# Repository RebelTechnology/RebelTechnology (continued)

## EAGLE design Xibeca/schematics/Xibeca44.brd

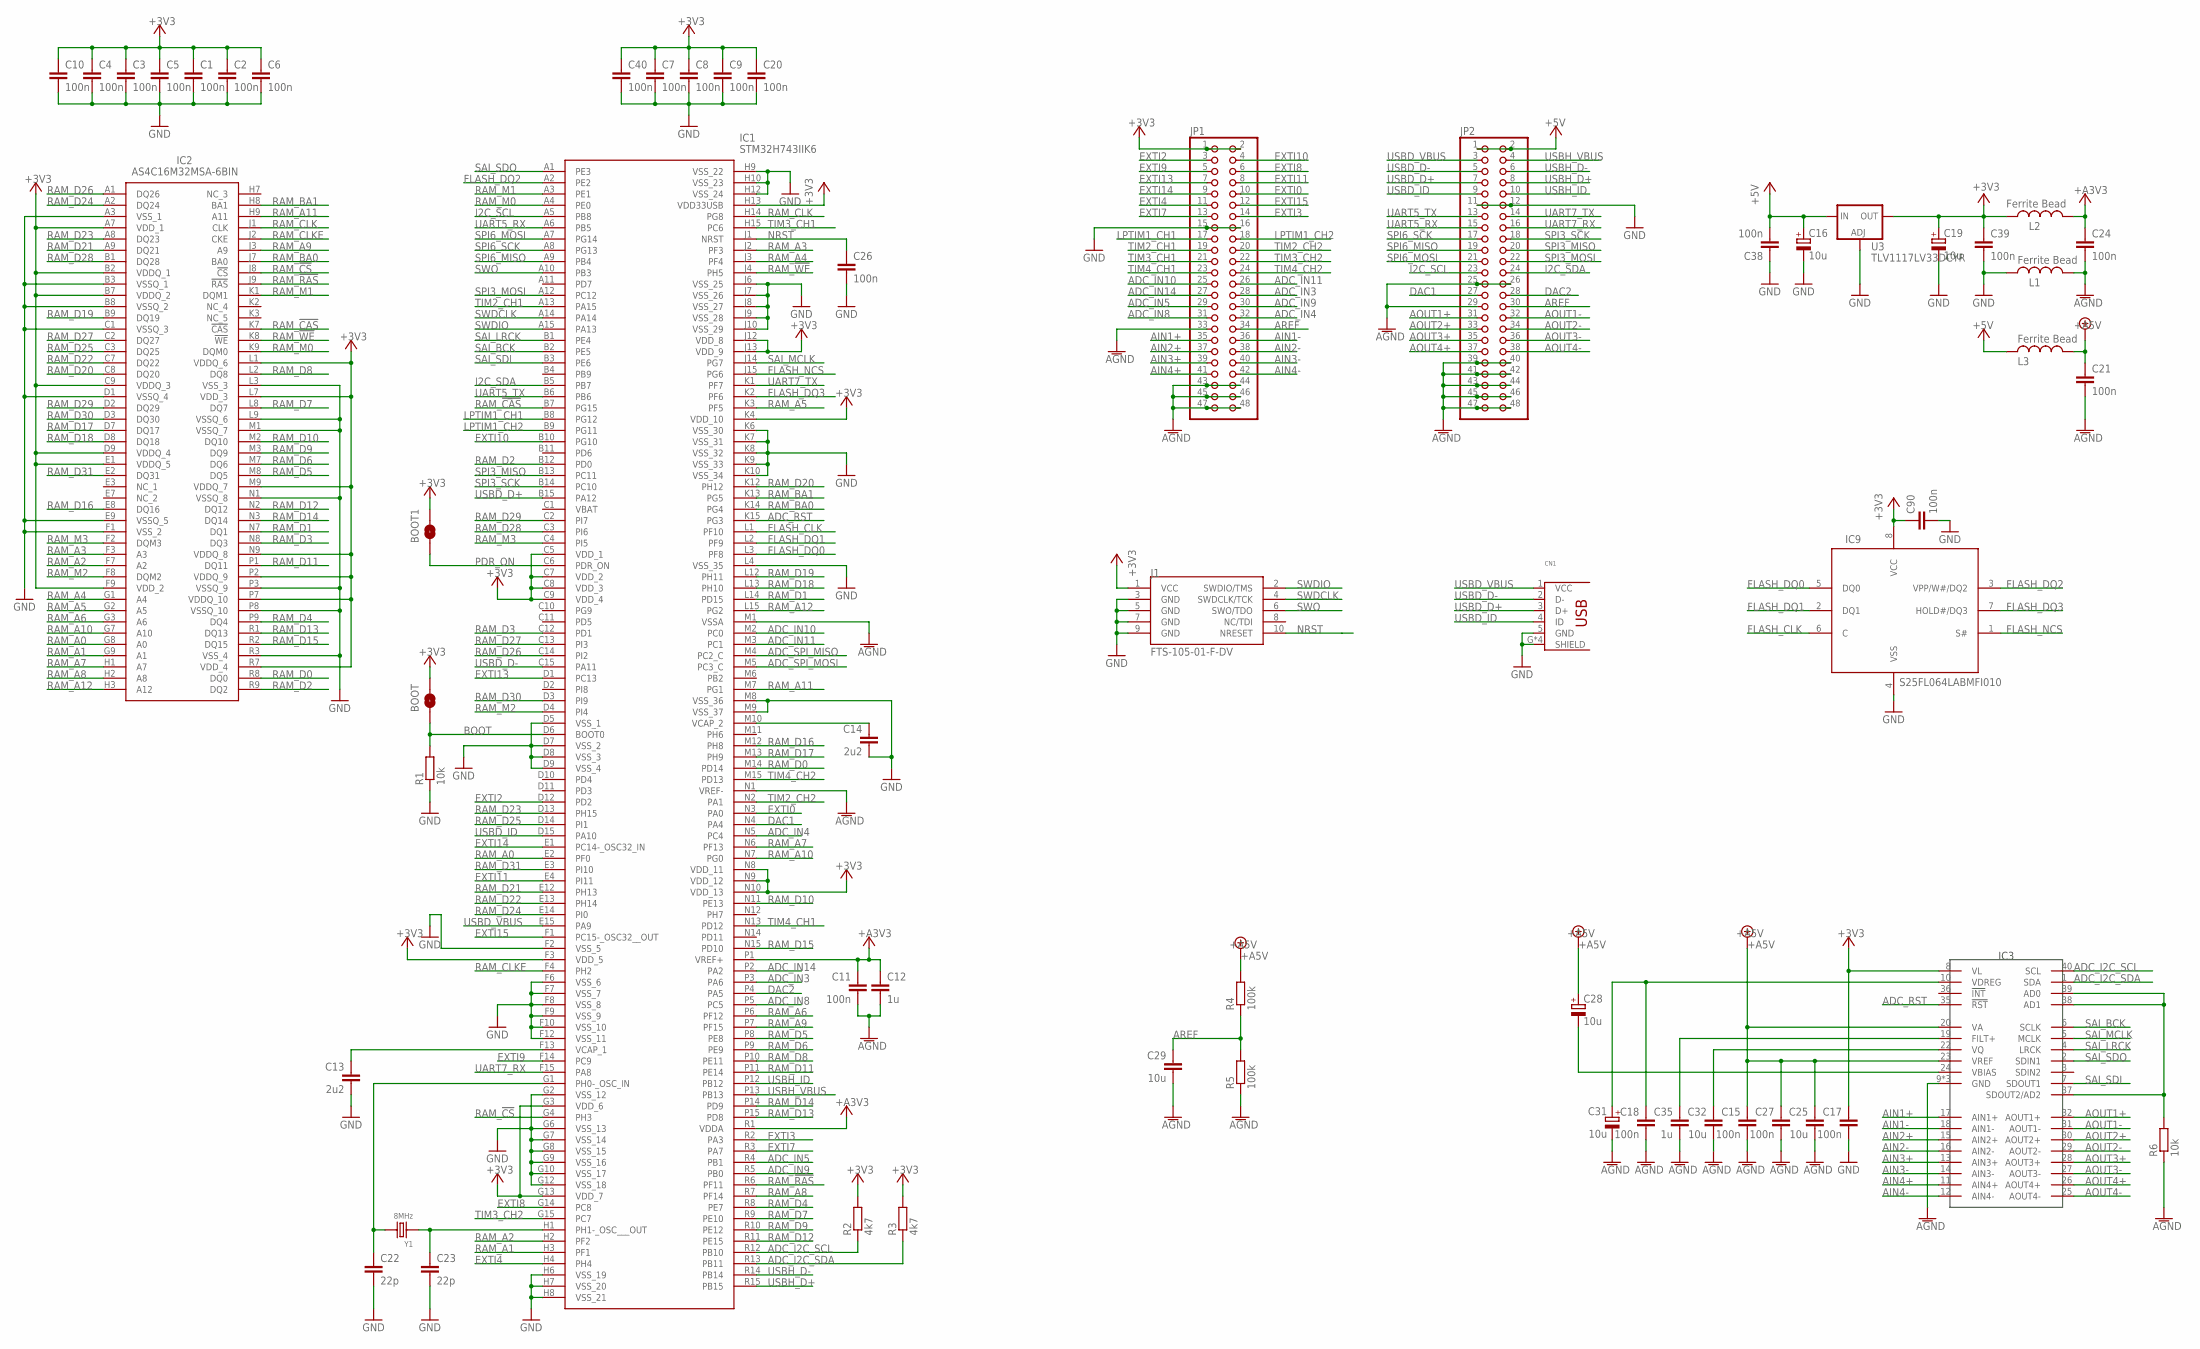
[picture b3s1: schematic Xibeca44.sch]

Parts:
BOOT, BOOT1: SOLDERJUMPERNO; SJ_2S-NO
C1, C2, C3, C4, C5, C6, C7, C8, C9, C10, C11, C15, C17, C18, C20, C21, C24, C26, C27, C38, C39, C40, C90: 100n; C0402
C12, C35: 1u; C0603
C13, C14: 2u2; C0402
C16, C19, C28, C31: 10u; UD-4X5,8_NICHICON
C22, C23: 22p; C0402
C25, C29, C32: 10u; C0603
CN1: USB_HRS_ZX62-B-5PA(11)MICRO.B; HRS_ZX62RD-AB-5P8
IC1: STM32H743IIK6; BGA201C65P15X15_1000X1000X60
IC2: AS4C16M32MSA-6BIN; BGA90C80P9X15_800X1300X100
IC3: CS4244; QFN50P600X600X100-41N
IC9: S25FL064LABMFI010; SO8W
J1: FTS-105-01-F-DV; 2X5_1.27MM_SMD
JP1, JP2: PINHD-2X24; 2X24
L1, L2, L3: Ferrite Bead; 0603
R1, R6: 10k; R0402
R2, R3: 4k7; R0402
R4, R5: 100k; R0402
U3: TLV1117LV33DCYR; SOT223
Y1: 8MHz; X2-SMD-5.0X3.2X1.3MM

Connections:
+3V3: BOOT.1, BOOT1.1, C1.1, C2.1, C3.1, C4.1, C5.1, C6.1, C7.1, C8.1, C9.1, C10.1, C17.1, C19.+, C20.1, C39.1, C40.1, C90.1, IC1.C5 (VDD_1), IC1.C7 (VDD_2), IC1.C8 (VDD_3), IC1.C9 (VDD_4), IC1.F3 (VDD_5), IC1.G3 (VDD_6), IC1.G13 (VDD_7), IC1.H13 (VDD33USB), IC1.J12 (VDD_8), IC1.J13 (VDD_9), IC1.K4 (VDD_10), IC1.N8 (VDD_11), IC1.N9 (VDD_12), IC1.N10 (VDD_13), IC2.A7 (VDD_1), IC2.B2 (VDDQ_1), IC2.B7 (VDDQ_2), IC2.C9 (VDDQ_3), IC2.D9 (VDDQ_4), IC2.E1 (VDDQ_5), IC2.F9 (VDD_2), IC2.L1 (VDDQ_6), IC2.L7 (VDD_3), IC2.M9 (VDDQ_7), IC2.N9 (VDDQ_8), IC2.P2 (VDDQ_9), IC2.P7 (VDDQ_10), IC2.R7 (VDD_4), IC3.8 (VL), IC9.8 (VCC), J1.1 (VCC), JP1.1, JP1.2, L2.2, R2.2, R3.2, U3.4 (OUT)
+5V: C16.+, C38.2, JP2.1, JP2.2, L3.2, U3.3 (IN)
+A3V3: C11.1, C12.1, C24.1, IC1.P1 (VREF+), IC1.R1 (VDDA), L2.1
+A5V: C15.1, C21.1, C25.1, C27.1, C28.+, IC3.20 (VA), IC3.23 (VREF), L3.1, R4.2
ADC_I2C_SCL: IC1.R12 (PB10), IC3.40 (SCL), R2.1
ADC_I2C_SDA: IC1.R13 (PB11), IC3.1 (SDA), R3.1
ADC_IN3: IC1.P3 (PA6), JP1.28
ADC_IN4: IC1.N5 (PC4), JP1.32
ADC_IN5: IC1.R4 (PB1), JP1.29
ADC_IN8: IC1.P5 (PC5), JP1.31
ADC_IN9: IC1.R5 (PB0), JP1.30
ADC_IN10: IC1.M2 (PC0), JP1.25
ADC_IN11: IC1.M3 (PC1), JP1.26
ADC_IN14: IC1.P2 (PA2), JP1.27
ADC_RST: IC1.K15 (PG3), IC3.35 (!RST)
ADC_SPI_MISO: IC1.M4 (PC2_C)
ADC_SPI_MOSI: IC1.M5 (PC3_C)
AGND: C11.2, C12.2, C15.2, C18.2, C21.2, C24.2, C25.2, C27.2, C29.2, C31.-, C32.2, C35.2, IC1.M1 (VSSA), IC1.N1 (VREF-), IC3.9 (GND), IC3.21 (GND), IC3.41 (GND), JP1.33, JP1.43, JP1.44, JP1.45, JP1.46, JP1.47, JP1.48, JP2.25, JP2.26, JP2.29, JP2.39, JP2.40, JP2.41, JP2.42, JP2.43, JP2.44, JP2.45, JP2.46, JP2.47, JP2.48, L1.1, R5.1, R6.1
AIN1+: IC3.17 (AIN1+), JP1.35
AIN1-: IC3.18 (AIN1-), JP1.36
AIN2+: IC3.15 (AIN2+), JP1.37
AIN2-: IC3.16 (AIN2-), JP1.38
AIN3+: IC3.13 (AIN3+), JP1.39
AIN3-: IC3.14 (AIN3-), JP1.40
AIN4+: IC3.11 (AIN4+), JP1.41
AIN4-: IC3.12 (AIN4-), JP1.42
AOUT1+: IC3.32 (AOUT1+), JP2.31
AOUT1-: IC3.31 (AOUT1-), JP2.32
AOUT2+: IC3.30 (AOUT2+), JP2.33
AOUT2-: IC3.29 (AOUT2-), JP2.34
AOUT3+: IC3.28 (AOUT3+), JP2.35
AOUT3-: IC3.27 (AOUT3-), JP2.36
AOUT4+: IC3.26 (AOUT4+), JP2.37
AOUT4-: IC3.25 (AOUT4-), JP2.38
AREF: C29.1, JP1.34, JP2.30, R4.1, R5.2
BOOT: BOOT.2, IC1.D6 (BOOT0), R1.2
DAC1: IC1.N4 (PA4), JP2.27
DAC2: IC1.P4 (PA5), JP2.28
EXTI0: IC1.N3 (PA0), JP1.10
EXTI2: IC1.D12 (PD2), JP1.3
EXTI3: IC1.R2 (PA3), JP1.14
EXTI4: IC1.H4, JP1.11
EXTI7: IC1.R3 (PA7), JP1.13
EXTI8: IC1.G14 (PC8), JP1.6
EXTI9: IC1.F14 (PC9), JP1.5
EXTI10: IC1.B10 (PG10), JP1.4
EXTI11: IC1.E4 (PI11), JP1.8
EXTI13: IC1.D1 (PC13), JP1.7
EXTI14: IC1.E1 (PC14-_OSC32_IN), JP1.9
EXTI15: IC1.F1 (PC15-_OSC32__OUT), JP1.12
FLASH_CLK: IC1.L1 (PF10), IC9.6 (C)
FLASH_DQ0: IC1.L3 (PF8), IC9.5 (DQ0)
FLASH_DQ1: IC1.L2 (PF9), IC9.2 (DQ1)
FLASH_DQ2: IC1.A2 (PE2), IC9.3 (VPP/W#/DQ2)
FLASH_DQ3: IC1.K2 (PF6), IC9.7 (HOLD#/DQ3)
FLASH_NCS: IC1.J15 (PG6), IC9.1 (S#)
GND: C1.2, C2.2, C3.2, C4.2, C5.2, C6.2, C7.2, C8.2, C9.2, C10.2, C13.2, C14.2, C16.-, C17.2, C19.-, C20.2, C22.2, C23.2, C26.2, C38.1, C39.2, C40.2, C90.2, CN1.5 (GND), CN1.G (SHIELD), CN1.G2 (SHIELD), CN1.G3 (SHIELD), CN1.G4 (SHIELD), IC1.D5 (VSS_1), IC1.D7 (VSS_2), IC1.D8 (VSS_3), IC1.D9 (VSS_4), IC1.F2 (VSS_5), IC1.F6 (VSS_6), IC1.F7 (VSS_7), IC1.F8 (VSS_8), IC1.F9 (VSS_9), IC1.F10 (VSS_10), IC1.F12 (VSS_11), IC1.G2 (VSS_12), IC1.G6 (VSS_13), IC1.G7 (VSS_14), IC1.G8 (VSS_15), IC1.G9 (VSS_16), IC1.G10 (VSS_17), IC1.G12 (VSS_18), IC1.H6 (VSS_19), IC1.H7 (VSS_20), IC1.H8 (VSS_21), IC1.H9 (VSS_22), IC1.H10 (VSS_23), IC1.H12 (VSS_24), IC1.J6 (VSS_25), IC1.J7 (VSS_26), IC1.J8 (VSS_27), IC1.J9 (VSS_28), IC1.J10 (VSS_29), IC1.K6 (VSS_30), IC1.K7 (VSS_31), IC1.K8 (VSS_32), IC1.K9 (VSS_33), IC1.K10 (VSS_34), IC1.L4 (VSS_35), IC1.M8 (VSS_36), IC1.M9 (VSS_37), IC2.A3 (VSS_1), IC2.B3 (VSSQ_1), IC2.B8 (VSSQ_2), IC2.C1 (VSSQ_3), IC2.D1 (VSSQ_4), IC2.E9 (VSSQ_5), IC2.F1 (VSS_2), IC2.L3 (VSS_3), IC2.L9 (VSSQ_6), IC2.M1 (VSSQ_7), IC2.N1 (VSSQ_8), IC2.P3 (VSSQ_9), IC2.P8 (VSSQ_10), IC2.R3 (VSS_4), IC9.4 (VSS), J1.3 (GND), J1.5 (GND), J1.7 (GND), J1.9 (GND), JP1.15, JP1.16, JP2.11, JP2.12, L1.2, R1.1, U3.1 (ADJ)
I2C_SCL: IC1.A5 (PB8), JP2.23
I2C_SDA: IC1.B5 (PB7), JP2.24
LPTIM1_CH1: IC1.B8 (PG12), JP1.17
LPTIM1_CH2: IC1.B9 (PG11), JP1.18
unnamed: C14.1, IC1.M10 (VCAP_2)
unnamed: C28.-, IC3.24 (VBIAS)
unnamed: C18.1, C31.+, IC3.10 (VDREG)
unnamed: C35.1, IC3.19 (FILT+)
unnamed: C32.1, IC3.22 (VQ)
unnamed: IC3.37 (SDOUT2/AD2), IC3.38 (AD1), IC3.39 (AD0), R6.2
unnamed: C13.1, IC1.F13 (VCAP_1)
unnamed: C23.1, IC1.H1 (PH1-_OSC___OUT), Y1.1
unnamed: C22.1, IC1.G1 (PH0-_OSC_IN), Y1.2
NRST: C26.1, IC1.J1 (NRST), J1.10 (NRESET)
PDR_ON: BOOT1.2, IC1.C6 (PDR_ON)
RAM_!CAS: IC1.B7 (PG15), IC2.K7 (!CAS)
RAM_!CS: IC1.G4 (PH3), IC2.J8 (!CS)
RAM_!RAS: IC1.R6 (PF11), IC2.J9 (!RAS)
RAM_!WE: IC1.J4 (PH5), IC2.K8 (!WE)
RAM_A0: IC1.E2 (PF0), IC2.G8 (A0)
RAM_A1: IC1.H3 (PF1), IC2.G9 (A1)
RAM_A2: IC1.H2 (PF2), IC2.F7 (A2)
RAM_A3: IC1.J2 (PF3), IC2.F3 (A3)
RAM_A4: IC1.J3 (PF4), IC2.G1 (A4)
RAM_A5: IC1.K3 (PF5), IC2.G2 (A5)
RAM_A6: IC1.P6 (PF12), IC2.G3 (A6)
RAM_A7: IC1.N6 (PF13), IC2.H1 (A7)
RAM_A8: IC1.R7 (PF14), IC2.H2 (A8)
RAM_A9: IC1.P7 (PF15), IC2.J3 (A9)
RAM_A10: IC1.N7 (PG0), IC2.G7 (A10)
RAM_A11: IC1.M7 (PG1), IC2.H9 (A11)
RAM_A12: IC1.L15 (PG2), IC2.H3 (A12)
RAM_BA0: IC1.K14 (PG4), IC2.J7 (BA0)
RAM_BA1: IC1.K13 (PG5), IC2.H8 (BA1)
RAM_CLK: IC1.H14 (PG8), IC2.J1 (CLK)
RAM_CLKE: IC1.F4 (PH2), IC2.J2 (CKE)
RAM_D0: IC1.M14 (PD14), IC2.R8 (DQ0)
RAM_D1: IC1.L14 (PD15), IC2.N7 (DQ1)
RAM_D2: IC1.B12 (PD0), IC2.R9 (DQ2)
RAM_D3: IC1.C12 (PD1), IC2.N8 (DQ3)
RAM_D4: IC1.R8 (PE7), IC2.P9 (DQ4)
RAM_D5: IC1.P8 (PE8), IC2.M8 (DQ5)
RAM_D6: IC1.P9 (PE9), IC2.M7 (DQ6)
RAM_D7: IC1.R9 (PE10), IC2.L8 (DQ7)
RAM_D8: IC1.P10 (PE11), IC2.L2 (DQ8)
RAM_D9: IC1.R10 (PE12), IC2.M3 (DQ9)
RAM_D10: IC1.N11 (PE13), IC2.M2 (DQ10)
RAM_D11: IC1.P11 (PE14), IC2.P1 (DQ11)
RAM_D12: IC1.R11 (PE15), IC2.N2 (DQ12)
RAM_D13: IC1.P15 (PD8), IC2.R1 (DQ13)
RAM_D14: IC1.P14 (PD9), IC2.N3 (DQ14)
RAM_D15: IC1.N15 (PD10), IC2.R2 (DQ15)
RAM_D16: IC1.M12 (PH8), IC2.E8 (DQ16)
RAM_D17: IC1.M13 (PH9), IC2.D7 (DQ17)
RAM_D18: IC1.L13 (PH10), IC2.D8 (DQ18)
RAM_D19: IC1.L12 (PH11), IC2.B9 (DQ19)
RAM_D20: IC1.K12 (PH12), IC2.C8 (DQ20)
RAM_D21: IC1.E12 (PH13), IC2.A9 (DQ21)
RAM_D22: IC1.E13 (PH14), IC2.C7 (DQ22)
RAM_D23: IC1.D13 (PH15), IC2.A8 (DQ23)
RAM_D24: IC1.E14 (PI0), IC2.A2 (DQ24)
RAM_D25: IC1.D14 (PI1), IC2.C3 (DQ25)
RAM_D26: IC1.C14 (PI2), IC2.A1 (DQ26)
RAM_D27: IC1.C13 (PI3), IC2.C2 (DQ27)
RAM_D28: IC1.C3 (PI6), IC2.B1 (DQ28)
RAM_D29: IC1.C2 (PI7), IC2.D2 (DQ29)
RAM_D30: IC1.D3 (PI9), IC2.D3 (DQ30)
RAM_D31: IC1.E3 (PI10), IC2.E2 (DQ31)
RAM_M0: IC1.A4 (PE0), IC2.K9 (DQM0)
RAM_M1: IC1.A3 (PE1), IC2.K1 (DQM1)
RAM_M2: IC1.D4 (PI4), IC2.F8 (DQM2)
RAM_M3: IC1.C4 (PI5), IC2.F2 (DQM3)
SAI_BCK: IC1.B2 (PE5), IC3.6 (SCLK)
SAI_LRCK: IC1.B1 (PE4), IC3.4 (LRCK)
SAI_MCLK: IC1.J14 (PG7), IC3.5 (MCLK)
SAI_SDI: IC1.B3 (PE6), IC3.7 (SDOUT1)
SAI_SDO: IC1.A1 (PE3), IC3.2 (SDIN1)
SPI3_MISO: IC1.B13 (PC11), JP2.20
SPI3_MOSI: IC1.A12 (PC12), JP2.22
SPI3_SCK: IC1.B14 (PC10), JP2.18
SPI6_MISO: IC1.A9 (PB4), JP2.19
SPI6_MOSI: IC1.A7 (PG14), JP2.21
SPI6_SCK: IC1.A8 (PG13), JP2.17
SWDCLK: IC1.A14, J1.4 (SWDCLK/TCK)
SWDIO: IC1.A15 (PA13), J1.2 (SWDIO/TMS)
SWO: IC1.A10 (PB3), J1.6 (SWO/TDO)
TIM2_CH1: IC1.A13 (PA15), JP1.19
TIM2_CH2: IC1.N2 (PA1), JP1.20
TIM3_CH1: IC1.H15 (PC6), JP1.21
TIM3_CH2: IC1.G15 (PC7), JP1.22
TIM4_CH1: IC1.N13 (PD12), JP1.23
TIM4_CH2: IC1.M15 (PD13), JP1.24
UART5_RX: IC1.A6 (PB5), JP2.15
UART5_TX: IC1.B6, JP2.13
UART7_RX: IC1.F15 (PA8), JP2.16
UART7_TX: IC1.K1 (PF7), JP2.14
USBD_D+: CN1.3 (D+), IC1.B15 (PA12), JP2.7
USBD_D-: CN1.2 (D-), IC1.C15 (PA11), JP2.5
USBD_ID: CN1.4 (ID), IC1.D15 (PA10), JP2.9
USBD_VBUS: CN1.1 (VCC), IC1.E15 (PA9), JP2.3
USBH_D+: IC1.R15 (PB15), JP2.8
USBH_D-: IC1.R14 (PB14), JP2.6
USBH_ID: IC1.P12 (PB12), JP2.10
USBH_VBUS: IC1.P13 (PB13), JP2.4

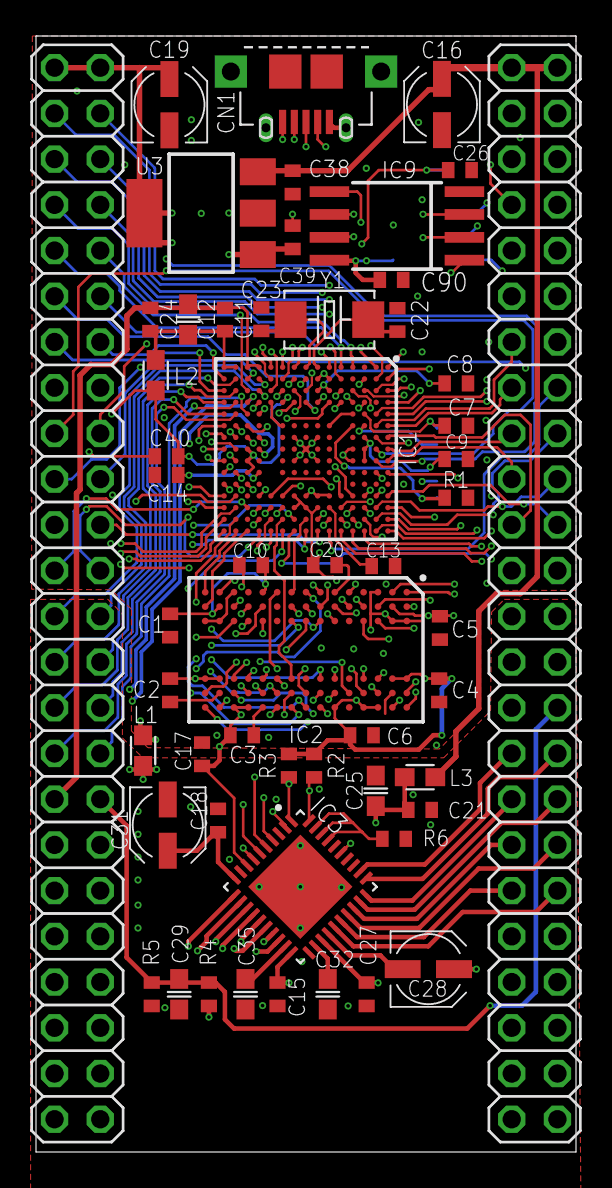
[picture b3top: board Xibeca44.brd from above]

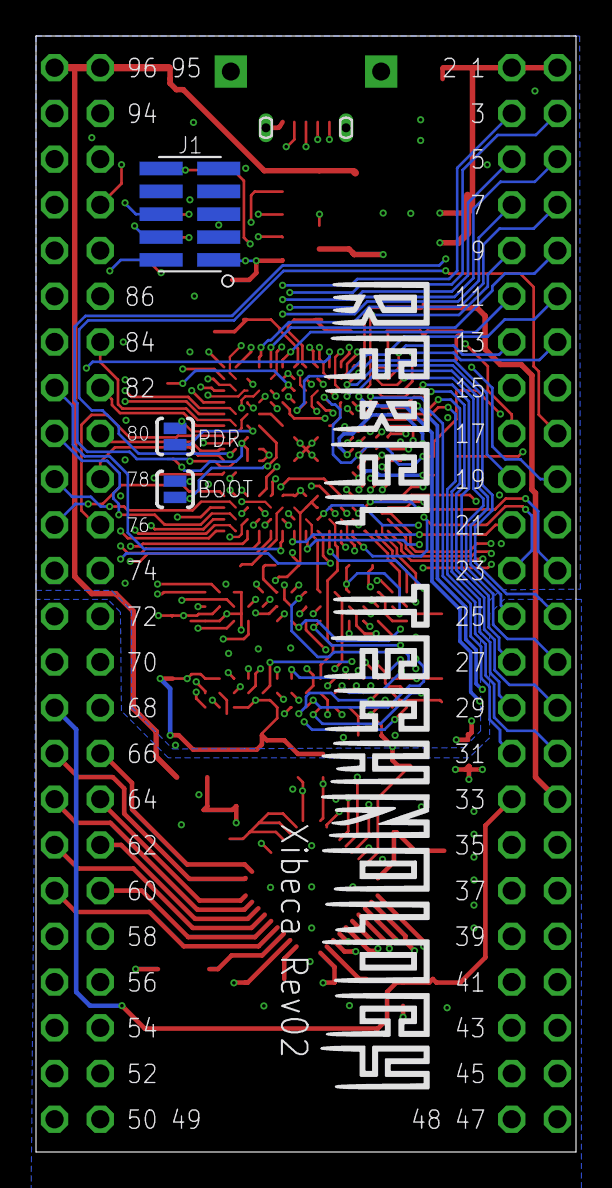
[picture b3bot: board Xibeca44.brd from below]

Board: 4 copper layers, 30.0 x 62.0 mm, 57 parts (3 on the bottom side), 159 nets.

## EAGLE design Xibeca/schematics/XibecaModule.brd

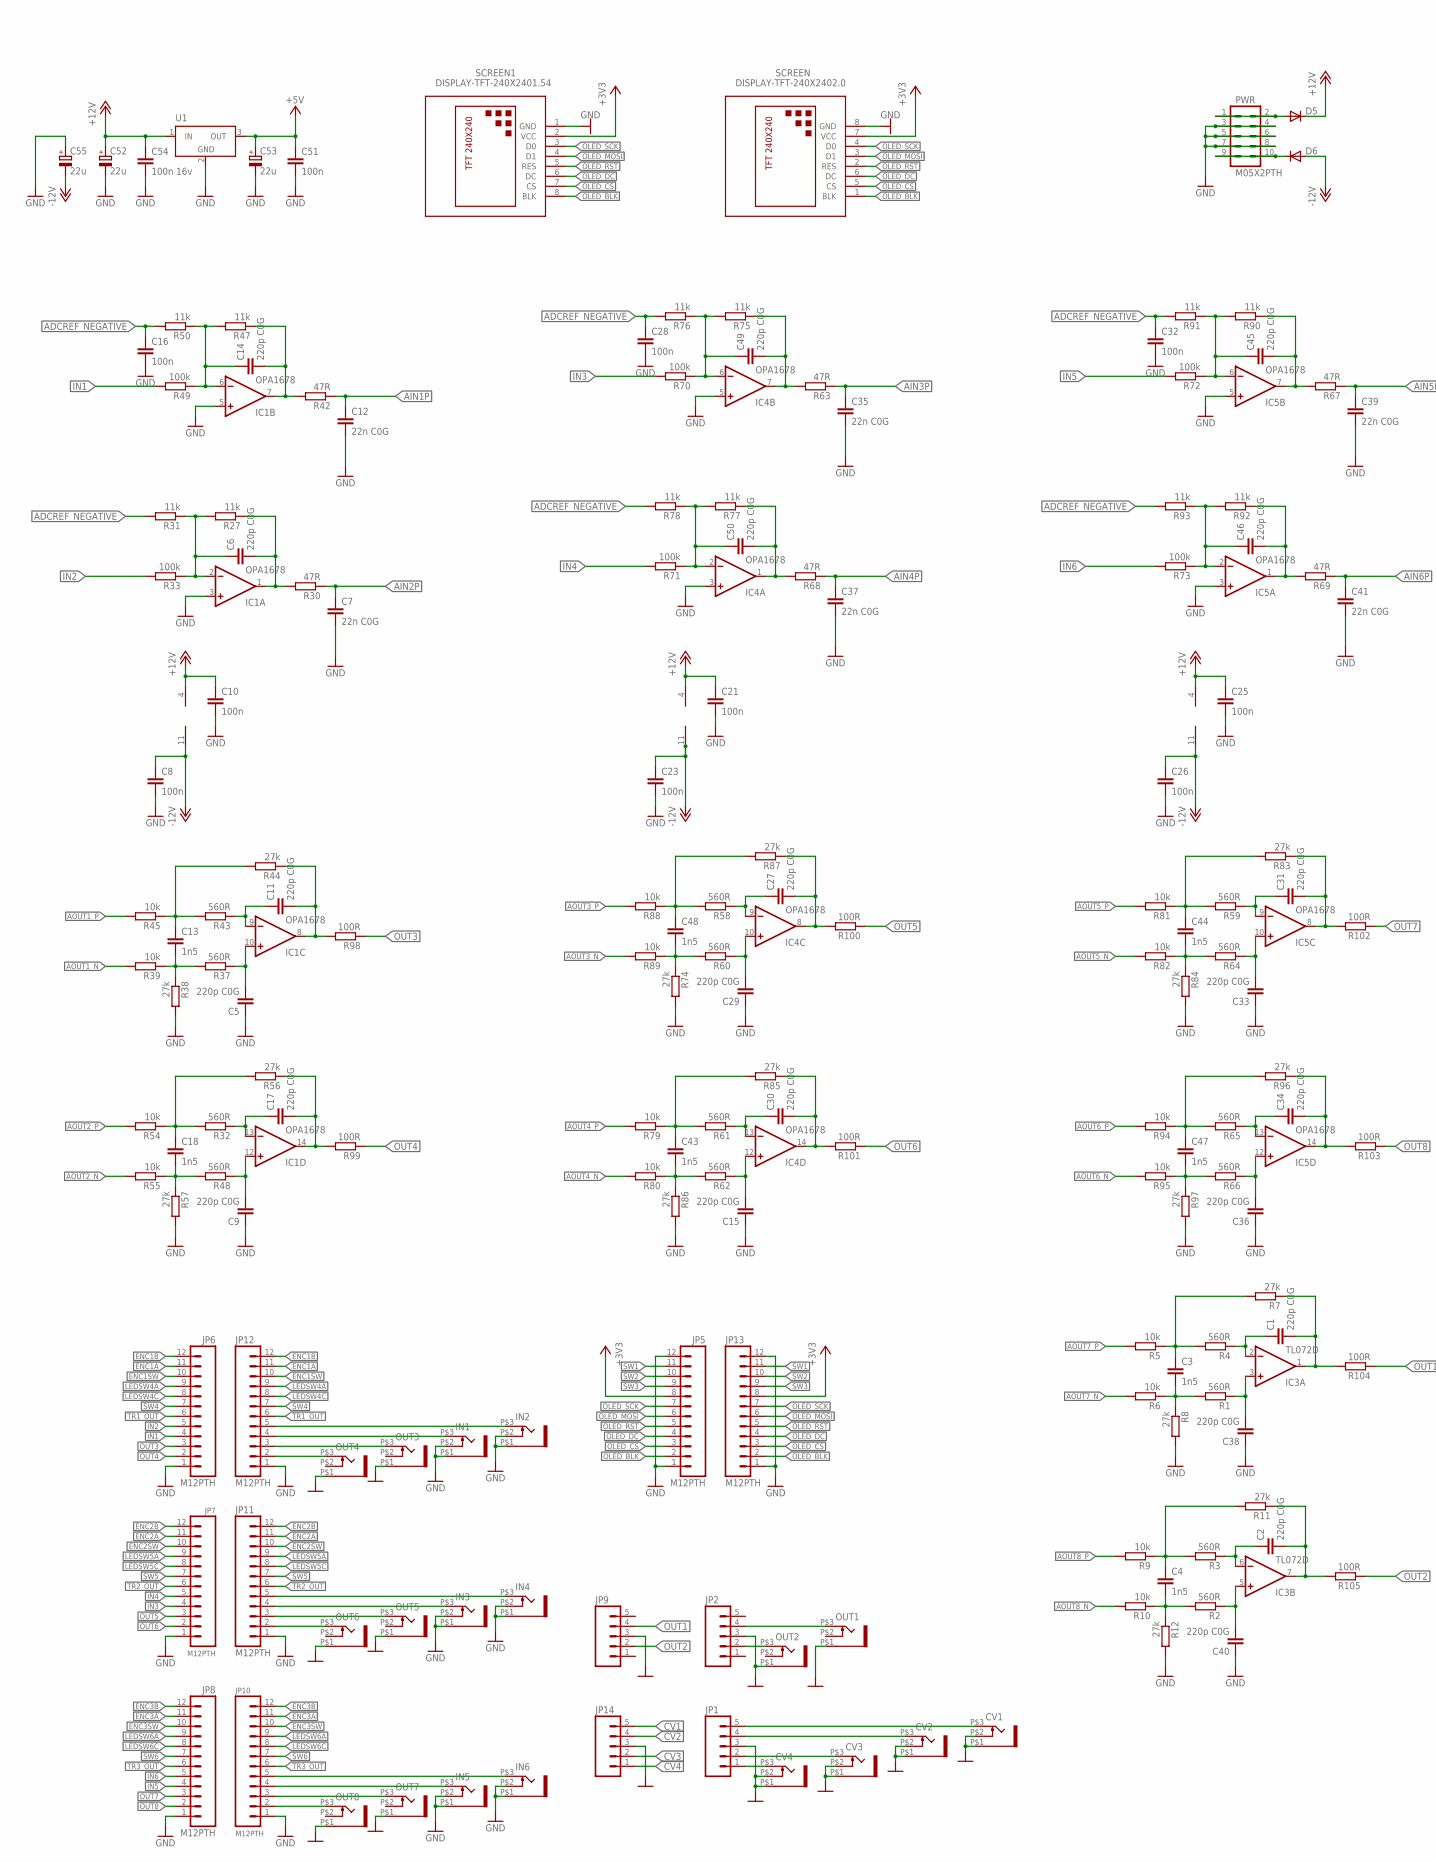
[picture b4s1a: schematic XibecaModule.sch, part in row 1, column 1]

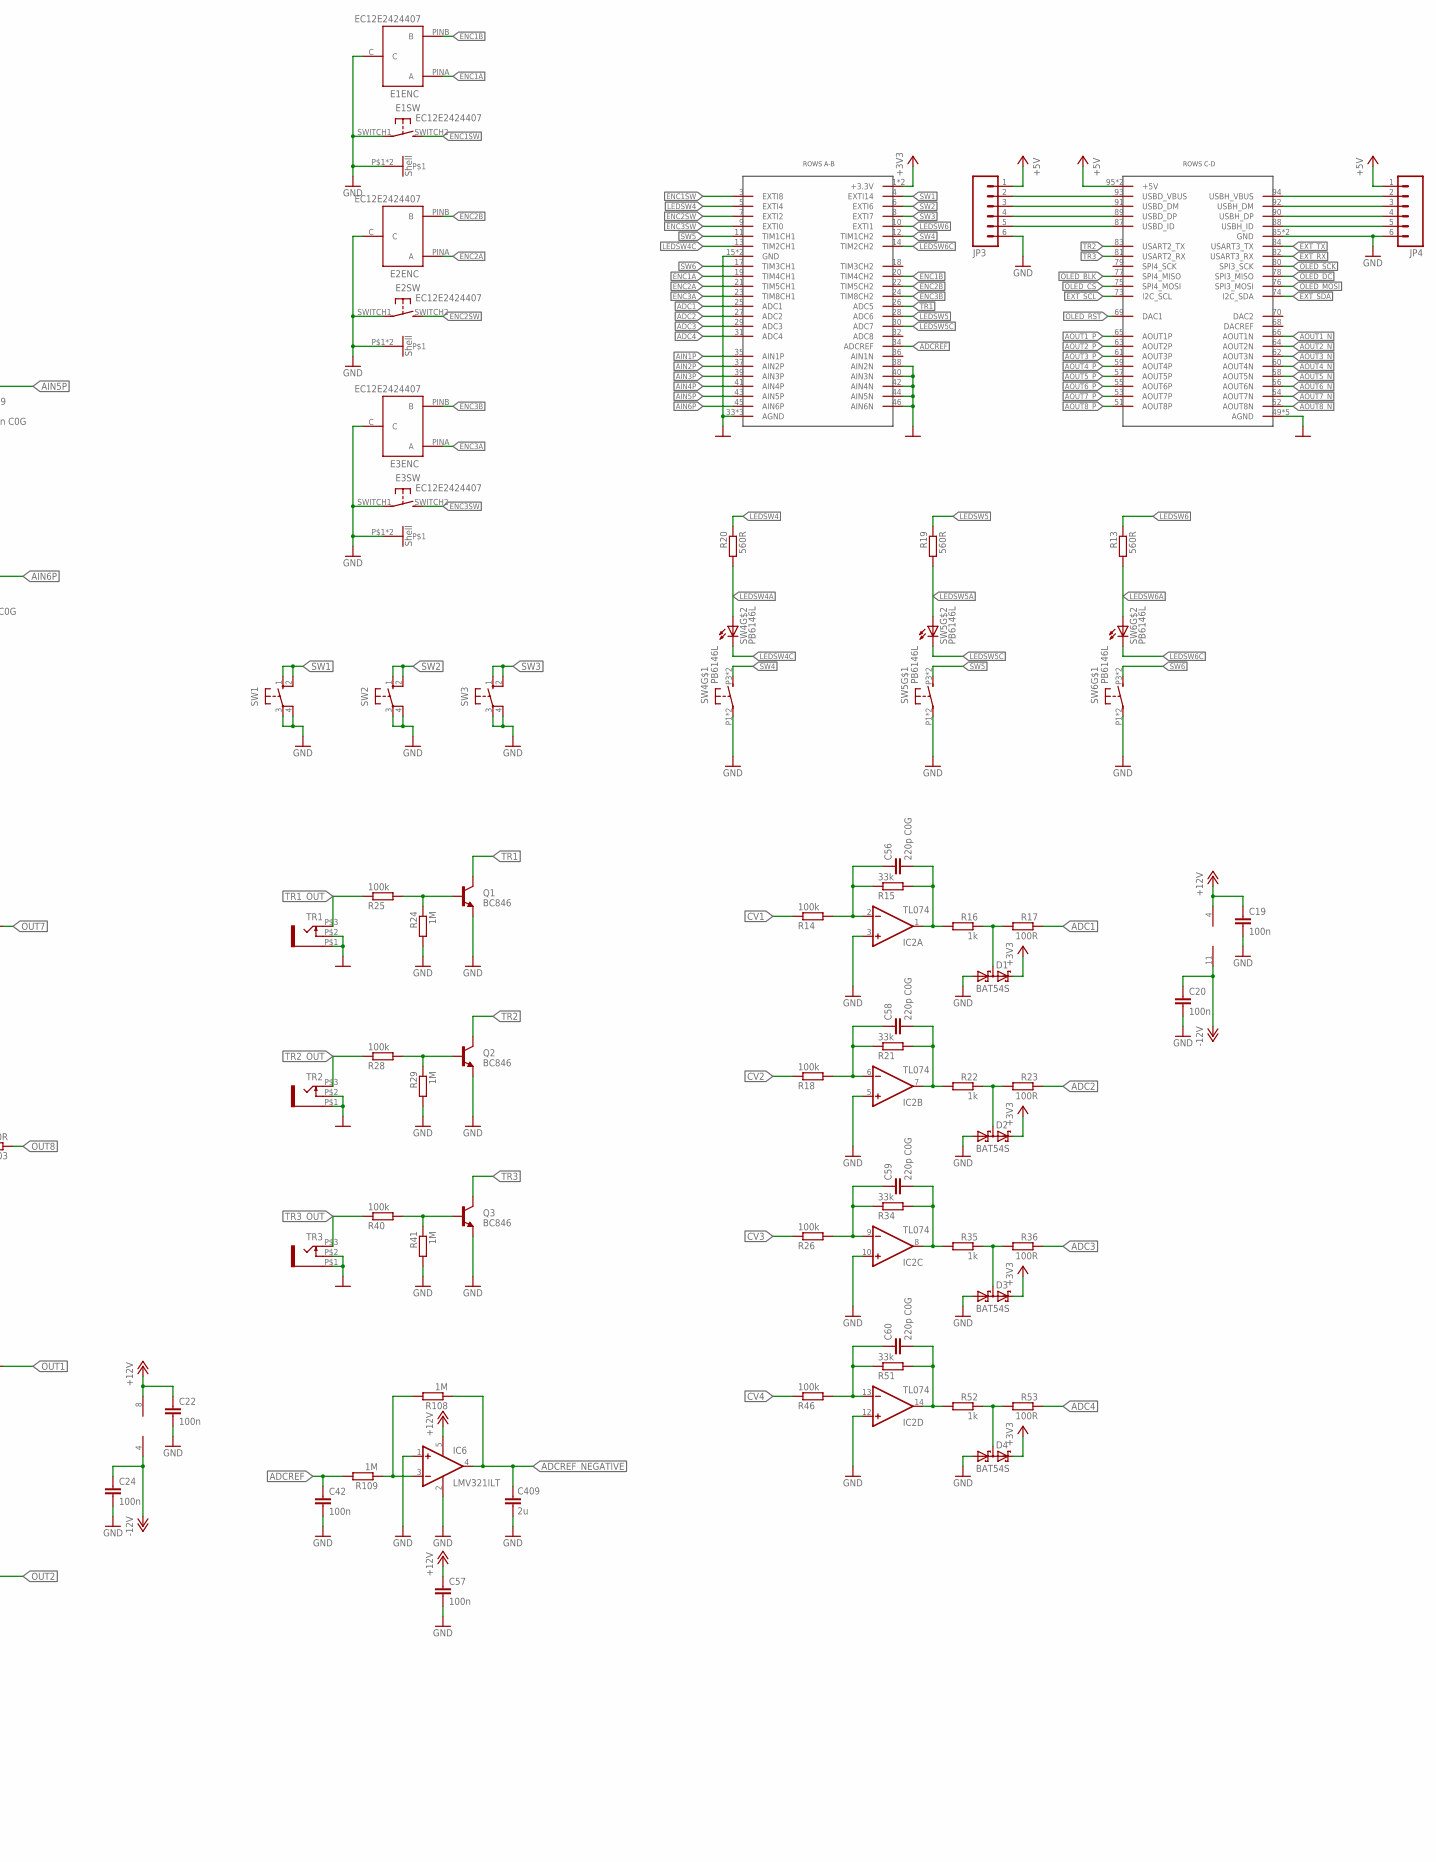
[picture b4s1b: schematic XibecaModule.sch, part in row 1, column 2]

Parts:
C1, C2, C5, C6, C9, C11, C14, C15, C17, C27, C29, C30, C31, C33, C34, C36, C38, C40, C45, C46, C49, C50, C56, C58, C59, C60: 220p C0G; C0603
C3, C4, C13, C18, C43, C44, C47, C48: 1n5; C0603
C7, C12, C35, C37, C39, C41: 22n C0G; C0603
C8, C10, C16, C19, C20, C21, C22, C23, C24, C25, C26, C28, C32, C42, C51, C57: 100n; C0603
C52, C53, C55: 22u; E5-8,5
C54: 100n 16v; C0603
C409: 2u; C0603
CV1, CV2, CV3, CV4: THONKICONN
D1, D2, D3, D4: BAT54S; SOT23
D5, D6: DIODE1N4001; DIODE-1N4001
E1, E2, E3: EC12E2424407
IC1, IC4, IC5: OPA1678; SO14
IC2: TL074; SO14
IC3: TL072D; SO08
IC6: LMV321ILT; SOT23-5
IN1, IN2, IN3, IN4, IN5, IN6: THONKICONN
JP1, JP2, JP9, JP14: M05PTH; 1X05
JP3, JP4: M06SIP; 1X06
JP5, JP6, JP7, JP8, JP10, JP11, JP12, JP13: M12PTH; 1X12
OUT1, OUT2, OUT3, OUT4, OUT5, OUT6, OUT7, OUT8: THONKICONN
PWR: M05X2PTH; AVR_ICSP
Q1, Q2, Q3: BC846; SOT23
R1, R2, R3, R4, R32, R37, R43, R48, R58, R59, R60, R61, R62, R64, R65, R66: 560R; R0603
R5, R6, R9, R10, R39, R45, R54, R55, R79, R80, R81, R82, R88, R89, R94, R95: 10k; R0603
R7, R8, R11, R12, R38, R44, R56, R57, R74, R83, R84, R85, R86, R87, R96, R97: 27k; R0603
R13, R19, R20: 560R; 0603
R14, R18, R25, R26, R28, R40, R46: 100k; 0603
R15, R21, R34, R51: 33k; 0603
R16, R22, R35, R52: 1k; 0603
R17, R23, R36, R53: 100R; 0603
R24, R29, R41: 1M; 0603
R27, R31, R47, R50, R75, R76, R77, R78, R90, R91, R92, R93: 11k; R0603
R30, R42, R63, R67, R68, R69: 47R; R0603
R33, R49, R70, R71, R72, R73: 100k; R0603
R98, R99, R100, R101, R102, R103, R104, R105: 100R; R0603
R108, R109: 1M; R0603
SCREEN: DISPLAY-TFT-240X2402.0; DISPLAY-TFT-240X320-2.0"
SCREEN1: DISPLAY-TFT-240X2401.54; DISPLAY-TFT-240X240-1.54"
SW1, SW2, SW3: 10-XX; B3F-10XX
SW4, SW5, SW6: PB6146L
TR1, TR2, TR3: THONKICONN
U1: TSR-1-2450
U$2: NOCTUA2NOCTUA2; NOCTUA

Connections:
+3V3: D1.2 (C2), D2.2 (C2), D3.2 (C2), D4.2 (C2), JP5.8, JP13.8, SCREEN.7 (VCC), SCREEN1.2 (VCC), U$2.1 (+3.3V), U$2.2 (+3.3V)
+5V: C51.1, C53.+, JP3.1, JP4.1, U1.3 (OUT), U$2.95 (+5V), U$2.96 (+5V)
+12V: C10.1, C19.1, C21.1, C22.1, C25.1, C52.+, C54.1, C57.1, D5.C, IC1.4 (V+), IC2.4 (V+), IC3.8 (V+), IC4.4 (V+), IC5.4 (V+), IC6.5 (V+), U1.1 (IN)
-12V: C8.1, C20.1, C23.1, C24.1, C26.1, C55.-, D6.A, IC1.11 (V-), IC2.11 (V-), IC3.4 (V-), IC4.11 (V-), IC5.11 (V-)
ADC1: R17.1, U$2.25 (ADC1)
ADC2: R23.1, U$2.27 (ADC2)
ADC3: R36.1, U$2.29 (ADC3)
ADC4: R53.1, U$2.31 (ADC4)
ADCREF: C42.1, R109.2, U$2.34 (ADCREF)
ADCREF_NEGATIVE: C16.1, C28.1, C32.1, C409.1, IC6.4 (OUT), R31.2, R50.2, R76.2, R78.2, R91.2, R93.2, R108.1
AIN1P: C12.1, R42.1, U$2.35 (AIN1P)
AIN2P: C7.1, R30.1, U$2.37 (AIN2P)
AIN3P: C35.1, R63.1, U$2.39 (AIN3P)
AIN4P: C37.1, R68.1, U$2.41 (AIN4P)
AIN5P: C39.1, R67.1, U$2.43 (AIN5P)
AIN6P: C41.1, R69.1, U$2.45 (AIN6P)
AOUT1_N: R39.2, U$2.66 (AOUT1N)
AOUT1_P: R45.2, U$2.65 (AOUT1P)
AOUT2_N: R55.2, U$2.64 (AOUT2N)
AOUT2_P: R54.2, U$2.63 (AOUT2P)
AOUT3_N: R89.2, U$2.62 (AOUT3N)
AOUT3_P: R88.2, U$2.61 (AOUT3P)
AOUT4_N: R80.2, U$2.60 (AOUT4N)
AOUT4_P: R79.2, U$2.59 (AOUT4P)
AOUT5_N: R82.2, U$2.58 (AOUT5N)
AOUT5_P: R81.2, U$2.57 (AOUT5P)
AOUT6_N: R95.2, U$2.56 (AOUT6N)
AOUT6_P: R94.2, U$2.55 (AOUT6P)
AOUT7_N: R6.2, U$2.54 (AOUT7N)
AOUT7_P: R5.2, U$2.53 (AOUT7P)
AOUT8_N: R10.2, U$2.52 (AOUT8N)
AOUT8_P: R9.2, U$2.51 (AOUT8P)
CV1: JP14.5, R14.1
CV2: JP14.4, R18.1
CV3: JP14.2, R26.1
CV4: JP14.1, R46.1
ENC1A: E1.PINA (A), JP6.11, JP12.11, U$2.19 (TIM4CH1)
ENC1B: E1.PINB (B), JP6.12, JP12.12, U$2.20 (TIM4CH2)
ENC1SW: E1.SWITCH2 (S), JP6.10, JP12.10, U$2.3 (EXTI8)
ENC2A: E2.PINA (A), JP7.11, JP11.11, U$2.21 (TIM5CH1)
ENC2B: E2.PINB (B), JP7.12, JP11.12, U$2.22 (TIM5CH2)
ENC2SW: E2.SWITCH2 (S), JP7.10, JP11.10, U$2.7 (EXTI2)
ENC3A: E3.PINA (A), JP8.11, JP10.11, U$2.23 (TIM8CH1)
ENC3B: E3.PINB (B), JP8.12, JP10.12, U$2.24 (TIM8CH2)
ENC3SW: E3.SWITCH2 (S), JP8.10, JP10.10, U$2.9 (EXTI0)
EXT_RX: U$2.82 (USART3_RX)
EXT_SCL: U$2.73 (I2C_SCL)
EXT_SDA: U$2.74 (I2C_SDA)
EXT_TX: U$2.84 (USART3_TX)
GND: C5.1, C7.2, C8.2, C9.1, C10.2, C12.2, C15.1, C16.2, C19.2, C20.2, C21.2, C22.2, C23.2, C24.2, C25.2, C26.2, C28.2, C29.1, C32.2, C33.1, C35.2, C36.1, C37.2, C38.1, C39.2, C40.1, C41.2, C42.2, C51.2, C52.-, C53.-, C54.2, C55.+, C57.2, C409.2, CV1.P$1 (5), CV1.P$2 (4), CV2.P$1 (5), CV2.P$2 (4), CV3.P$1 (5), CV3.P$2 (4), CV4.P$1 (5), CV4.P$2 (4), D1.1 (A1), D2.1 (A1), D3.1 (A1), D4.1 (A1), E1.C, E1.P$1, E1.P$2, E1.SWITCH1, E2.C, E2.P$1, E2.P$2, E2.SWITCH1, E3.C, E3.P$1, E3.P$2, E3.SWITCH1, IC1.3 (+IN), IC1.5 (+IN), IC2.3 (+IN), IC2.5 (+IN), IC2.10 (+IN), IC2.12 (+IN), IC4.3 (+IN), IC4.5 (+IN), IC5.3 (+IN), IC5.5 (+IN), IC6.1 (+IN), IC6.2 (V-), IN1.P$1 (5), IN1.P$2 (4), IN2.P$1 (5), IN2.P$2 (4), IN3.P$1 (5), IN3.P$2 (4), IN4.P$1 (5), IN4.P$2 (4), IN5.P$1 (5), IN5.P$2 (4), IN6.P$1 (5), IN6.P$2 (4), JP1.3, JP2.3, JP3.6, JP4.6, JP5.1, JP5.12, JP6.1, JP7.1, JP8.1, JP9.3, JP10.1, JP11.1, JP12.1, JP13.1, JP13.12, JP14.3, OUT1.P$1 (5), OUT2.P$1 (5), OUT3.P$1 (5), OUT4.P$1 (5), OUT5.P$1 (5), OUT6.P$1 (5), OUT7.P$1 (5), OUT8.P$1 (5), PWR.3, PWR.4, PWR.5, PWR.6, PWR.7, PWR.8, Q1.2 (E), Q2.2 (E), Q3.2 (E), R8.2, R12.2, R24.2, R29.2, R38.2, R41.2, R57.2, R74.2, R84.2, R86.2, R97.2, SCREEN.8 (GND), SCREEN1.1 (GND), SW1.3, SW1.4 (P1), SW2.3, SW2.4 (P1), SW3.3, SW3.4 (P1), SW4.P1, SW4.P2, SW5.P1, SW5.P2, SW6.P1, SW6.P2, TR1.P$1 (5), TR1.P$2 (4), TR2.P$1 (5), TR2.P$2 (4), TR3.P$1 (5), TR3.P$2 (4), U1.2 (GND), U$2.15 (GND), U$2.16 (GND), U$2.33 (AGND), U$2.38 (AIN2N), U$2.40 (AIN3N), U$2.42 (AIN4N), U$2.44 (AIN5N), U$2.46 (AIN6N), U$2.47 (AGND), U$2.48 (AGND), U$2.49 (AGND), U$2.50 (AGND), U$2.67 (AGND), U$2.71 (AGND), U$2.72 (AGND), U$2.85 (GND), U$2.86 (GND)
IN1: JP6.4, R49.2
IN2: JP6.5, R33.2
IN3: JP7.4, R70.2
IN4: JP7.5, R71.2
IN5: JP8.4, R72.2
IN6: JP8.5, R73.2
LEDSW4: R20.1, U$2.5 (EXTI4)
LEDSW4A: JP6.9, JP12.9, R20.2, SW4.PL1 (A)
LEDSW4C: JP6.8, JP12.8, SW4.PL2 (C), U$2.13 (TIM2CH1)
LEDSW5: R19.1, U$2.28 (ADC6)
LEDSW5A: JP7.9, JP11.9, R19.2, SW5.PL1 (A)
LEDSW5C: JP7.8, JP11.8, SW5.PL2 (C), U$2.30 (ADC7)
LEDSW6: R13.1, U$2.10 (EXTI1)
LEDSW6A: JP8.9, JP10.9, R13.2, SW6.PL1 (A)
LEDSW6C: JP8.8, JP10.8, SW6.PL2 (C), U$2.14 (TIM2CH2)
unnamed: C17.2, IC1.14 (OUT), R56.1, R99.2
unnamed: C18.2, R48.2, R55.1, R57.1
unnamed: C18.1, R32.2, R54.1, R56.2
unnamed: C6.2, IC1.1 (OUT), R27.1, R30.2
unnamed: C17.1, IC1.13 (-IN), R32.1
unnamed: C6.1, IC1.2 (-IN), R27.2, R31.1, R33.1
unnamed: D6.C, PWR.9, PWR.10
unnamed: C9.2, IC1.12 (+IN), R48.1
unnamed: D5.A, PWR.1, PWR.2
unnamed: C34.2, IC5.14 (OUT), R96.1, R103.2
unnamed: C48.2, R60.2, R74.1, R89.1
unnamed: C48.1, R58.2, R87.2, R88.1
unnamed: C27.1, IC4.9 (-IN), R58.1
unnamed: C29.2, IC4.10 (+IN), R60.1
unnamed: C27.2, IC4.8 (OUT), R87.1, R100.2
unnamed: C30.2, IC4.14 (OUT), R85.1, R101.2
unnamed: C49.2, IC4.7 (OUT), R63.2, R75.1
unnamed: C49.1, IC4.6 (-IN), R70.1, R75.2, R76.1
unnamed: IN2.P$3 (3), JP12.5
unnamed: C50.2, IC4.1 (OUT), R68.2, R77.1
unnamed: C50.1, IC4.2 (-IN), R71.1, R77.2, R78.1
unnamed: C31.2, IC5.8 (OUT), R83.1, R102.2
unnamed: C43.2, R62.2, R80.1, R86.1
unnamed: C43.1, R61.2, R79.1, R85.2
unnamed: C30.1, IC4.13 (-IN), R61.1
unnamed: C15.2, IC4.12 (+IN), R62.1
unnamed: IC6.3 (-IN), R108.2, R109.1
unnamed: C1.2, IC3.1 (OUT), R7.1, R104.2
unnamed: C3.2, R1.2, R6.1, R8.1
unnamed: Q1.1 (B), R24.1, R25.2
unnamed: C3.1, R4.2, R5.1, R7.2
unnamed: C2.2, IC3.7 (OUT), R11.1, R105.2
unnamed: IN1.P$3 (3), JP12.4
unnamed: JP12.3, OUT3.P$3 (3)
unnamed: C44.2, R64.2, R82.1, R84.1
unnamed: C44.1, R59.2, R81.1, R83.2
unnamed: C31.1, IC5.9 (-IN), R59.1
unnamed: C33.2, IC5.10 (+IN), R64.1
unnamed: C11.2, IC1.8 (OUT), R44.1, R98.2
unnamed: Q2.1 (B), R28.2, R29.1
unnamed: C45.2, IC5.7 (OUT), R67.2, R90.1
unnamed: C45.1, IC5.6 (-IN), R72.1, R90.2, R91.1
unnamed: JP12.2, OUT4.P$3 (3)
unnamed: C46.2, IC5.1 (OUT), R69.2, R92.1
unnamed: C46.1, IC5.2 (-IN), R73.1, R92.2, R93.1
unnamed: JP11.2, OUT6.P$3 (3)
unnamed: C47.2, R66.2, R95.1, R97.1
unnamed: C47.1, R65.2, R94.1, R96.2
unnamed: C34.1, IC5.13 (-IN), R65.1
unnamed: C36.2, IC5.12 (+IN), R66.1
unnamed: JP11.3, OUT5.P$3 (3)
unnamed: C58.1, IC2.6 (-IN), R18.2, R21.1
unnamed: JP2.4, OUT1.P$3 (3)
unnamed: JP2.2, OUT2.P$3 (3)
unnamed: C56.1, IC2.2 (-IN), R14.2, R15.1
unnamed: IN3.P$3 (3), JP11.4
unnamed: Q3.1 (B), R40.2, R41.1
unnamed: C1.1, IC3.2 (-IN), R4.1
unnamed: C38.2, IC3.3 (+IN), R1.1
unnamed: IN4.P$3 (3), JP11.5
unnamed: C4.2, R2.2, R10.1, R12.1
unnamed: C4.1, R3.2, R9.1, R11.2
unnamed: C2.1, IC3.6 (-IN), R3.1
unnamed: C40.2, IC3.5 (+IN), R2.1
unnamed: JP10.2, OUT8.P$3 (3)
unnamed: C56.2, IC2.1 (OUT), R15.2, R16.2
unnamed: D1.3 (C1A2), R16.1, R17.2
unnamed: C58.2, IC2.7 (OUT), R21.2, R22.2
unnamed: D2.3 (C1A2), R22.1, R23.2
unnamed: C59.1, IC2.9 (-IN), R26.2, R34.1
unnamed: C59.2, IC2.8 (OUT), R34.2, R35.2
unnamed: D3.3 (C1A2), R35.1, R36.2
unnamed: C60.1, IC2.13 (-IN), R46.2, R51.1
unnamed: C60.2, IC2.14 (OUT), R51.2, R52.2
unnamed: D4.3 (C1A2), R52.1, R53.2
unnamed: JP3.2, U$2.93 (USBD_VBUS)
unnamed: JP3.3, U$2.91 (USBD_DM)
unnamed: JP3.4, U$2.89 (USBD_DP)
unnamed: JP3.5, U$2.87 (USBD_ID)
unnamed: JP4.5, U$2.88 (USBH_ID)
unnamed: JP4.4, U$2.90 (USBH_DP)
unnamed: JP4.3, U$2.92 (USBH_DM)
unnamed: JP4.2, U$2.94 (USBH_VBUS)
unnamed: JP10.3, OUT7.P$3 (3)
unnamed: IN5.P$3 (3), JP10.4
unnamed: IN6.P$3 (3), JP10.5
unnamed: CV4.P$3 (3), JP1.1
unnamed: CV1.P$3 (3), JP1.5
unnamed: CV2.P$3 (3), JP1.4
unnamed: CV3.P$3 (3), JP1.2
unnamed: C13.2, R37.2, R38.1, R39.1
unnamed: C13.1, R43.2, R44.2, R45.1
unnamed: C11.1, IC1.9 (-IN), R43.1
unnamed: C5.2, IC1.10 (+IN), R37.1
unnamed: C14.2, IC1.7 (OUT), R42.2, R47.1
unnamed: C14.1, IC1.6 (-IN), R47.2, R49.1, R50.1
OLED_BLK: JP5.2, JP13.2, SCREEN.1 (BLK), SCREEN1.8 (BLK), U$2.77 (SPI4_MISO)
OLED_CS: JP5.3, JP13.3, SCREEN.5 (CS), SCREEN1.7 (CS), U$2.75 (SPI4_MOSI)
OLED_DC: JP5.4, JP13.4, SCREEN.6 (DC), SCREEN1.6 (DC), U$2.78 (SPI3_MISO)
OLED_MOSI: JP5.6, JP13.6, SCREEN.3 (D1), SCREEN1.4 (D1), U$2.76 (SPI3_MOSI)
OLED_RST: JP5.5, JP13.5, SCREEN.2 (RES), SCREEN1.5 (RES), U$2.69 (DAC1)
OLED_SCK: JP5.7, JP13.7, SCREEN.4 (D0), SCREEN1.3 (D0), U$2.80 (SPI3_SCK)
OUT1: JP9.4, R104.1
OUT2: JP9.2, R105.1
OUT3: JP6.3, R98.1
OUT4: JP6.2, R99.1
OUT5: JP7.3, R100.1
OUT6: JP7.2, R101.1
OUT7: JP8.3, R102.1
OUT8: JP8.2, R103.1
SW1: JP5.11, JP13.11, SW1.1 (S), SW1.2 (S1), U$2.4 (EXTI14)
SW2: JP5.10, JP13.10, SW2.1 (S), SW2.2 (S1), U$2.6 (EXTI6)
SW3: JP5.9, JP13.9, SW3.1 (S), SW3.2 (S1), U$2.8 (EXTI7)
SW4: JP6.7, JP12.7, SW4.P3 (S), SW4.P4 (S), U$2.12 (TIM1CH2)
SW5: JP7.7, JP11.7, SW5.P3 (S), SW5.P4 (S), U$2.11 (TIM1CH1)
SW6: JP8.7, JP10.7, SW6.P3 (S), SW6.P4 (S), U$2.17 (TIM3CH1)
TR1: Q1.3 (C), U$2.26 (ADC5)
TR1_OUT: JP6.6, JP12.6, R25.1, TR1.P$3 (3)
TR2: Q2.3 (C), U$2.83 (USART2_TX)
TR2_OUT: JP7.6, JP11.6, R28.1, TR2.P$3 (3)
TR3: Q3.3 (C), U$2.81 (USART2_RX)
TR3_OUT: JP8.6, JP10.6, R40.1, TR3.P$3 (3)
